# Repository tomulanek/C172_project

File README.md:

# C172_project
Zde na GitHub budu dávat veškerou dokumentaci k mému prvnímu projektu Cessny172. Můj project můžete najít na adrese:https://projectcockpitc172.blogspot.com/
Kdo by měl zájem. je možno něco prodat.

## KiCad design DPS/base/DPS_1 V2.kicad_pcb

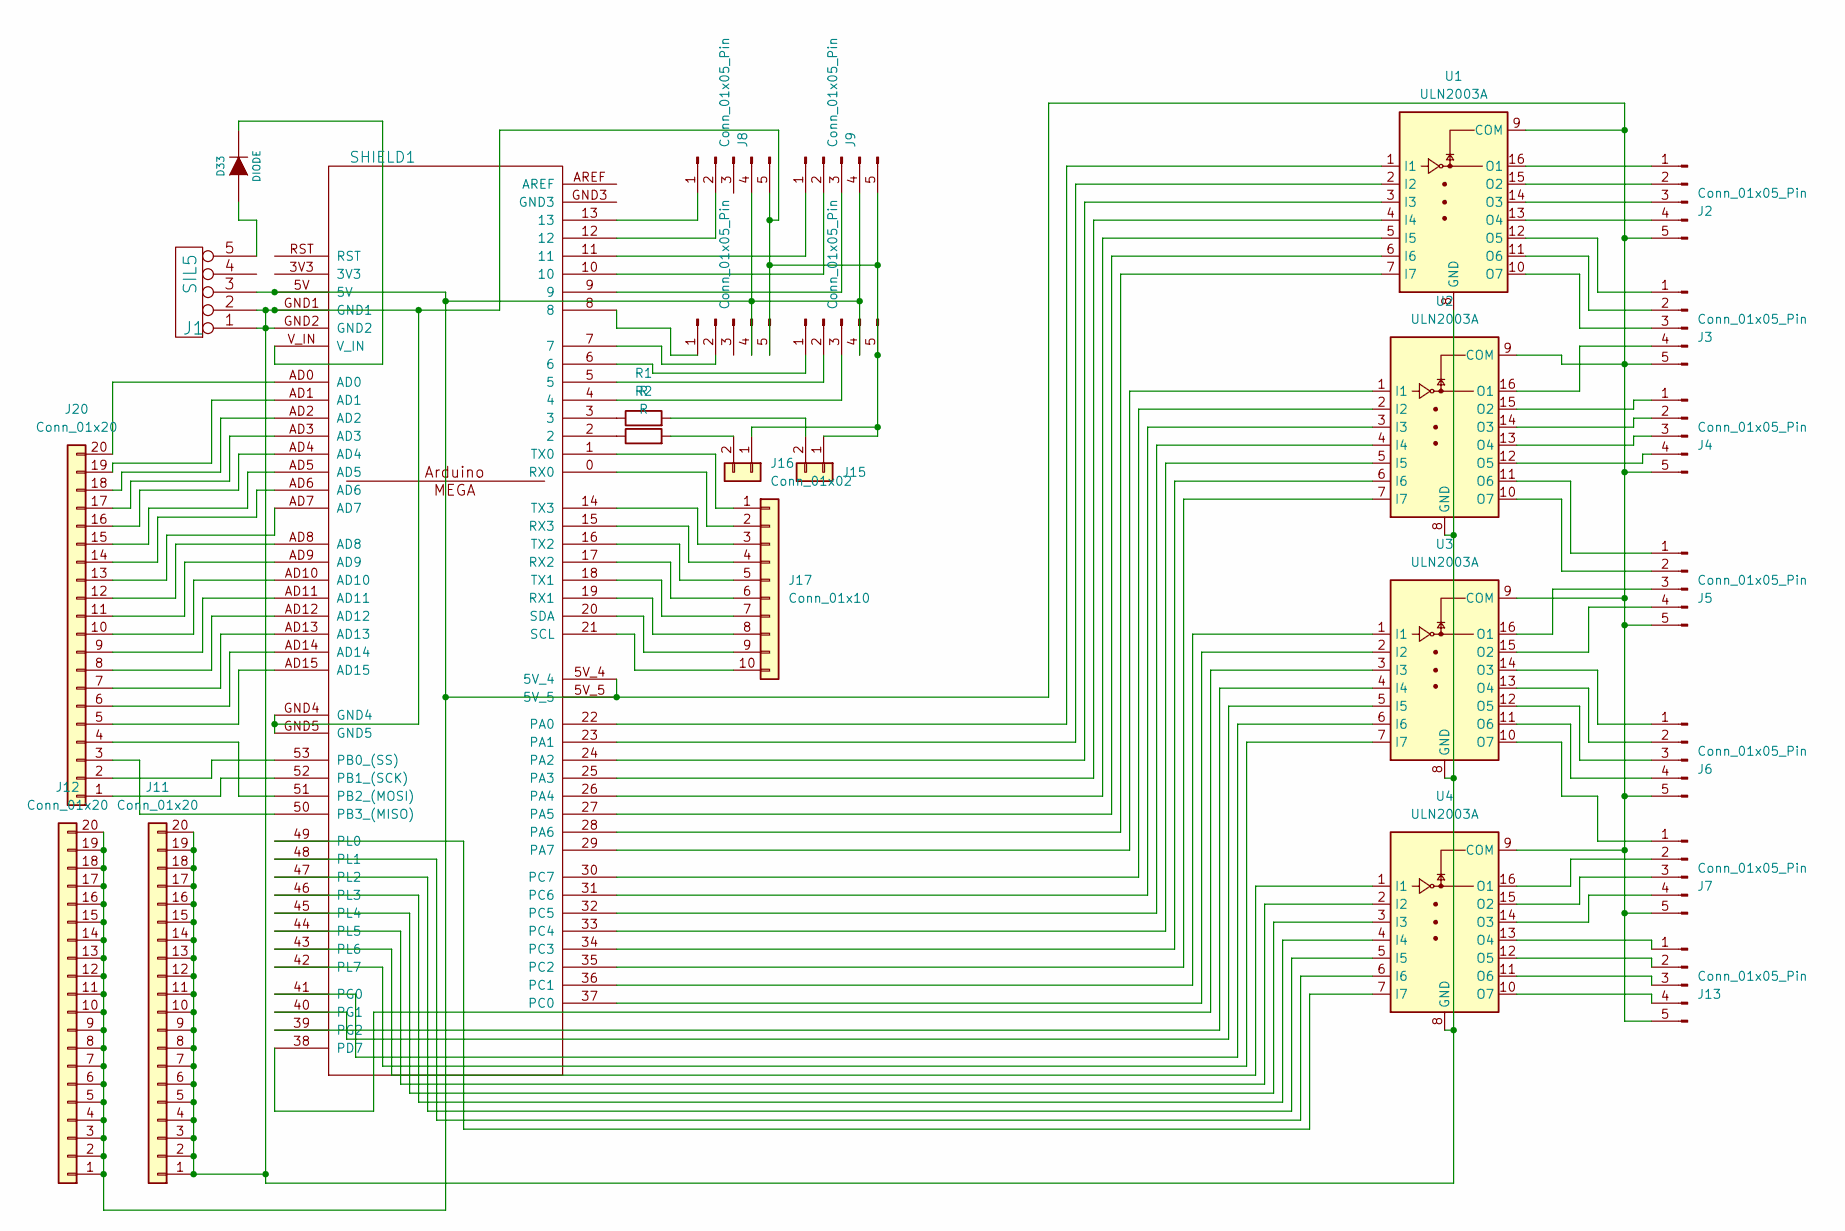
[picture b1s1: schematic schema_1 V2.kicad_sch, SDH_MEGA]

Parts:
D33: DIODE; D_0805_2012Metric
J1: SIL5; PinHeader_1x05_P2.54mm_Vertical
J2, J3, J4, J5, J6, J7, J8, J9, J10, J13, J14: Conn_01x05_Pin; PinHeader_1x05_P2.54mm_Vertical
J11, J12, J20: Conn_01x20; PinSocket_1x20_P2.54mm_Vertical
J15, J16: Conn_01x02; PinSocket_1x02_P2.54mm_Vertical
J17: Conn_01x10; PinSocket_1x10_P2.54mm_Vertical
R1, R2: R; R_0805_2012Metric
SHIELD1: ARDUINO_MEGA_SHIELD
U1, U2, U3, U4: ULN2003A; DIP-16_W7.62mm_LongPads

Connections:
unnamed: D33.1 (A), J1.5
unnamed: D33.2 (K), SHIELD1.V_IN
unnamed: J2.1, U1.16 (O1)
unnamed: J2.2, U1.15 (O2)
unnamed: J2.3, U1.14 (O3)
unnamed: J2.4, U1.13 (O4)
unnamed: J3.1, U1.12 (O5)
unnamed: J3.2, U1.11 (O6)
unnamed: J3.3, U1.10 (O7)
unnamed: J3.4, U2.16 (O1)
unnamed: J4.1, U2.15 (O2)
unnamed: J4.2, U2.14 (O3)
unnamed: J4.3, U2.13 (O4)
unnamed: J4.4, U2.12 (O5)
unnamed: J5.1, U2.11 (O6)
unnamed: J5.2, U2.10 (O7)
unnamed: J5.3, U3.16 (O1)
unnamed: J5.4, U3.15 (O2)
unnamed: J6.1, U3.14 (O3)
unnamed: J6.2, U3.13 (O4)
unnamed: J6.3, U3.12 (O5)
unnamed: J6.4, U3.11 (O6)
unnamed: J7.1, U3.10 (O7)
unnamed: J7.2, U4.16 (O1)
unnamed: J7.3, U4.15 (O2)
unnamed: J7.4, U4.14 (O3)
unnamed: J8.1, SHIELD1.13
unnamed: J8.2, SHIELD1.12
unnamed: J9.1, SHIELD1.11
unnamed: J9.2, SHIELD1.10
unnamed: J9.3, SHIELD1.9
unnamed: J10.1, SHIELD1.8
unnamed: J10.2, SHIELD1.7
unnamed: J1.3, J2.5, J3.5, J4.5, J5.5, J6.5, J7.5, J8.4, J9.4, J10.4, J12.1, J12.2, J12.3, J12.4, J12.5, J12.6, J12.7, J12.8, J12.9, J12.10, J12.11, J12.12, J12.13, J12.14, J12.15, J12.16, J12.17, J12.18, J12.19, J12.20, J13.5, J14.4, SHIELD1.5V, SHIELD1.5V_4, SHIELD1.5V_5, U1.9 (COM), U2.9 (COM), U3.9 (COM), U4.9 (COM)
unnamed: J1.1, J1.2, J8.5, J9.5, J10.5, J11.1, J11.2, J11.3, J11.4, J11.5, J11.6, J11.7, J11.8, J11.9, J11.10, J11.11, J11.12, J11.13, J11.14, J11.15, J11.16, J11.17, J11.18, J11.19, J11.20, J14.5, J15.1, J16.1, SHIELD1.GND1, SHIELD1.GND2, SHIELD1.GND4, SHIELD1.GND5, U1.8 (GND), U2.8 (GND), U3.8 (GND), U4.8 (GND)
unnamed: J13.1, U4.13 (O4)
unnamed: J13.2, U4.12 (O5)
unnamed: J13.3, U4.11 (O6)
unnamed: J13.4, U4.10 (O7)
unnamed: J14.1, SHIELD1.6
unnamed: J14.2, SHIELD1.5
unnamed: J14.3, SHIELD1.4
unnamed: J15.2, R1.2
unnamed: J16.2, R2.2
unnamed: J17.1, SHIELD1.1 (TX0)
unnamed: J17.2, SHIELD1.0 (RX0)
unnamed: J17.3, SHIELD1.14 (TX3)
unnamed: J17.4, SHIELD1.15 (RX3)
unnamed: J17.5, SHIELD1.16 (TX2)
unnamed: J17.6, SHIELD1.17 (RX2)
unnamed: J17.7, SHIELD1.18 (TX1)
unnamed: J17.8, SHIELD1.19 (RX1)
unnamed: J17.9, SHIELD1.20 (SDA)
unnamed: J17.10, SHIELD1.21 (SCL)
unnamed: J20.1, SHIELD1.52 (PB1_(SCK))
unnamed: J20.2, SHIELD1.53 (PB0_(SS))
unnamed: J20.3, SHIELD1.50 (PB3_(MISO))
unnamed: J20.4, SHIELD1.51 (PB2_(MOSI))
unnamed: J20.5, SHIELD1.AD15
unnamed: J20.6, SHIELD1.AD14
unnamed: J20.7, SHIELD1.AD13
unnamed: J20.8, SHIELD1.AD12
unnamed: J20.9, SHIELD1.AD11
unnamed: J20.10, SHIELD1.AD10
unnamed: J20.11, SHIELD1.AD9
unnamed: J20.12, SHIELD1.AD8
unnamed: J20.13, SHIELD1.AD7
unnamed: J20.14, SHIELD1.AD6
unnamed: J20.15, SHIELD1.AD5
unnamed: J20.16, SHIELD1.AD4
unnamed: J20.17, SHIELD1.AD3
unnamed: J20.18, SHIELD1.AD2
unnamed: J20.19, SHIELD1.AD1
unnamed: J20.20, SHIELD1.AD0
unnamed: R1.1, SHIELD1.3
unnamed: R2.1, SHIELD1.2
unnamed: SHIELD1.22 (PA0), U1.1 (I1)
unnamed: SHIELD1.23 (PA1), U1.2 (I2)
unnamed: SHIELD1.24 (PA2), U1.3 (I3)
unnamed: SHIELD1.25 (PA3), U1.4 (I4)
unnamed: SHIELD1.26 (PA4), U1.5 (I5)
unnamed: SHIELD1.27 (PA5), U1.6 (I6)
unnamed: SHIELD1.28 (PA6), U1.7 (I7)
unnamed: SHIELD1.29 (PA7), U2.1 (I1)
unnamed: SHIELD1.37 (PC0), U3.2 (I2)
unnamed: SHIELD1.36 (PC1), U3.1 (I1)
unnamed: SHIELD1.35 (PC2), U2.7 (I7)
unnamed: SHIELD1.34 (PC3), U2.6 (I6)
unnamed: SHIELD1.33 (PC4), U2.5 (I5)
unnamed: SHIELD1.32 (PC5), U2.4 (I4)
unnamed: SHIELD1.31 (PC6), U2.3 (I3)
unnamed: SHIELD1.30 (PC7), U2.2 (I2)
unnamed: SHIELD1.38 (PD7), U3.3 (I3)
unnamed: SHIELD1.41 (PG0), U3.6 (I6)
unnamed: SHIELD1.40 (PG1), U3.5 (I5)
unnamed: SHIELD1.39 (PG2), U3.4 (I4)
unnamed: SHIELD1.49 (PL0), U4.7 (I7)
unnamed: SHIELD1.48 (PL1), U4.6 (I6)
unnamed: SHIELD1.47 (PL2), U4.5 (I5)
unnamed: SHIELD1.46 (PL3), U4.4 (I4)
unnamed: SHIELD1.45 (PL4), U4.3 (I3)
unnamed: SHIELD1.44 (PL5), U4.2 (I2)
unnamed: SHIELD1.43 (PL6), U4.1 (I1)
unnamed: SHIELD1.42 (PL7), U3.7 (I7)

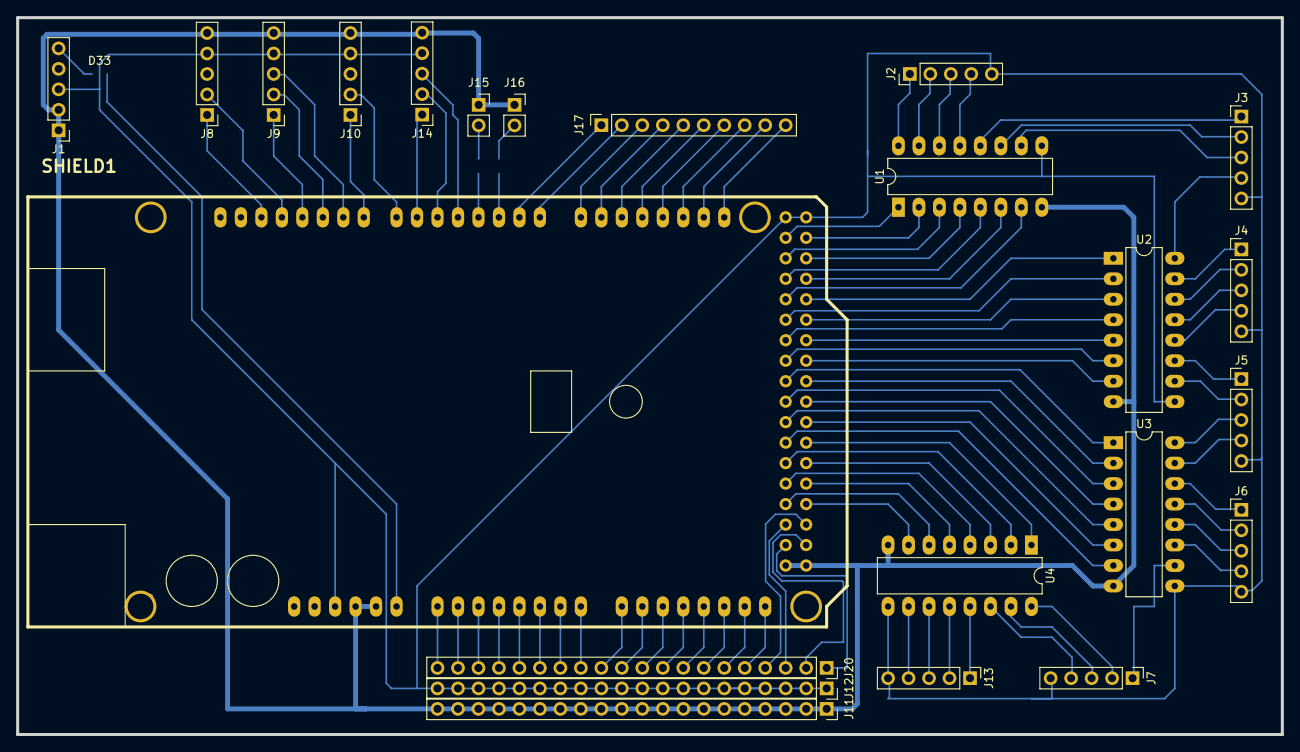
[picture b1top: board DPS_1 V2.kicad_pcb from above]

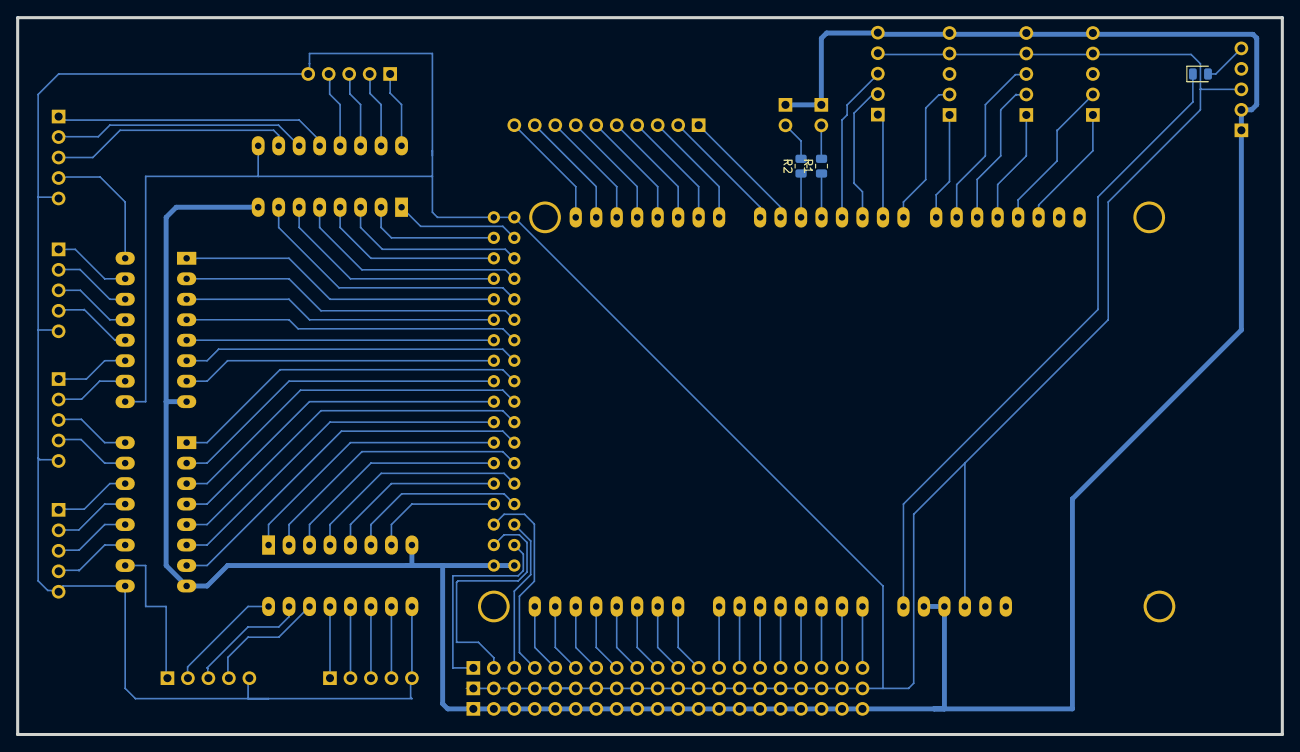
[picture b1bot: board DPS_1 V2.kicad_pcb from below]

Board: 2 copper layers, 156.8 x 88.9 mm, 26 parts (3 on the bottom side), 104 nets.

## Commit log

2023-09-03 rychloměr
2023-09-03 3D tisk STL
2023-09-03 Create 3
2023-09-03 Update rychloměr
2023-09-11 Create schema
